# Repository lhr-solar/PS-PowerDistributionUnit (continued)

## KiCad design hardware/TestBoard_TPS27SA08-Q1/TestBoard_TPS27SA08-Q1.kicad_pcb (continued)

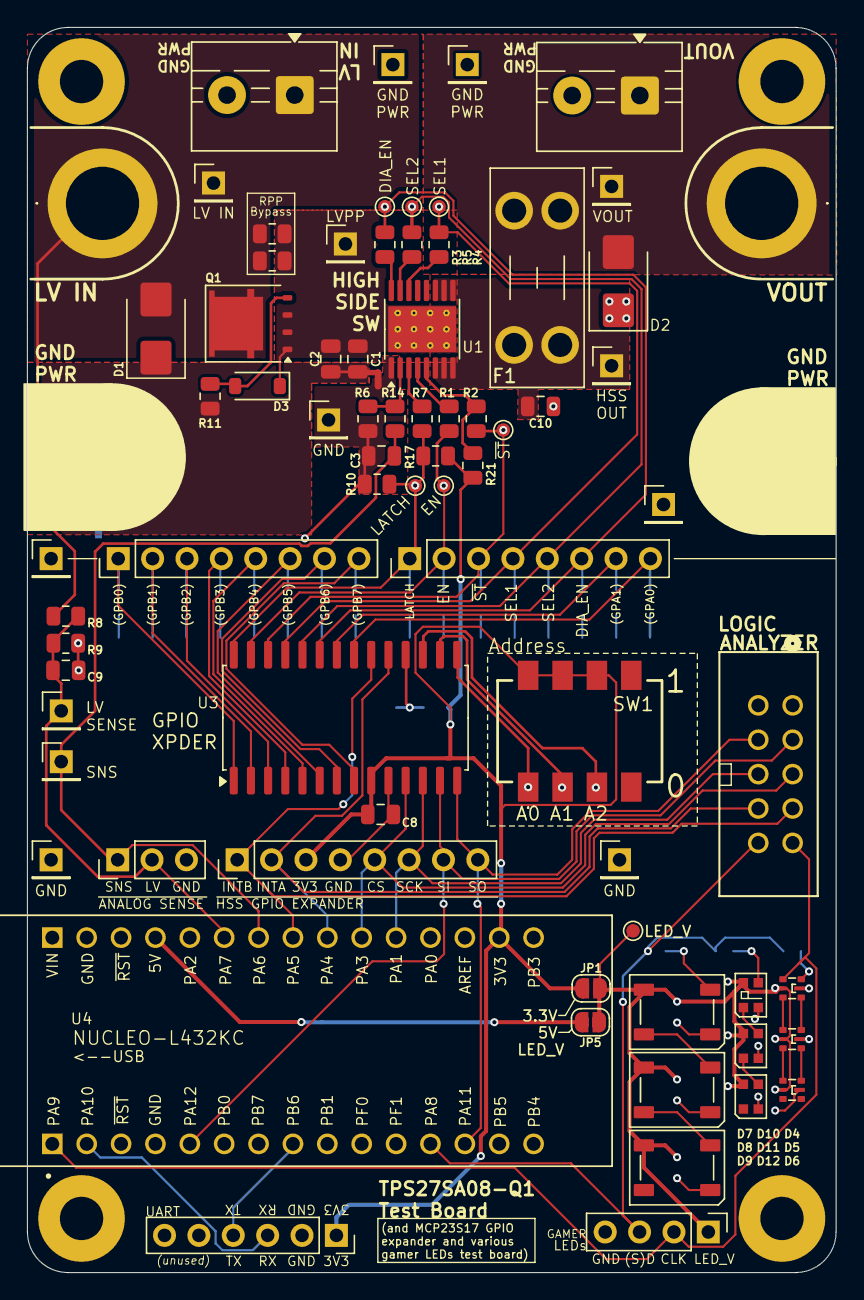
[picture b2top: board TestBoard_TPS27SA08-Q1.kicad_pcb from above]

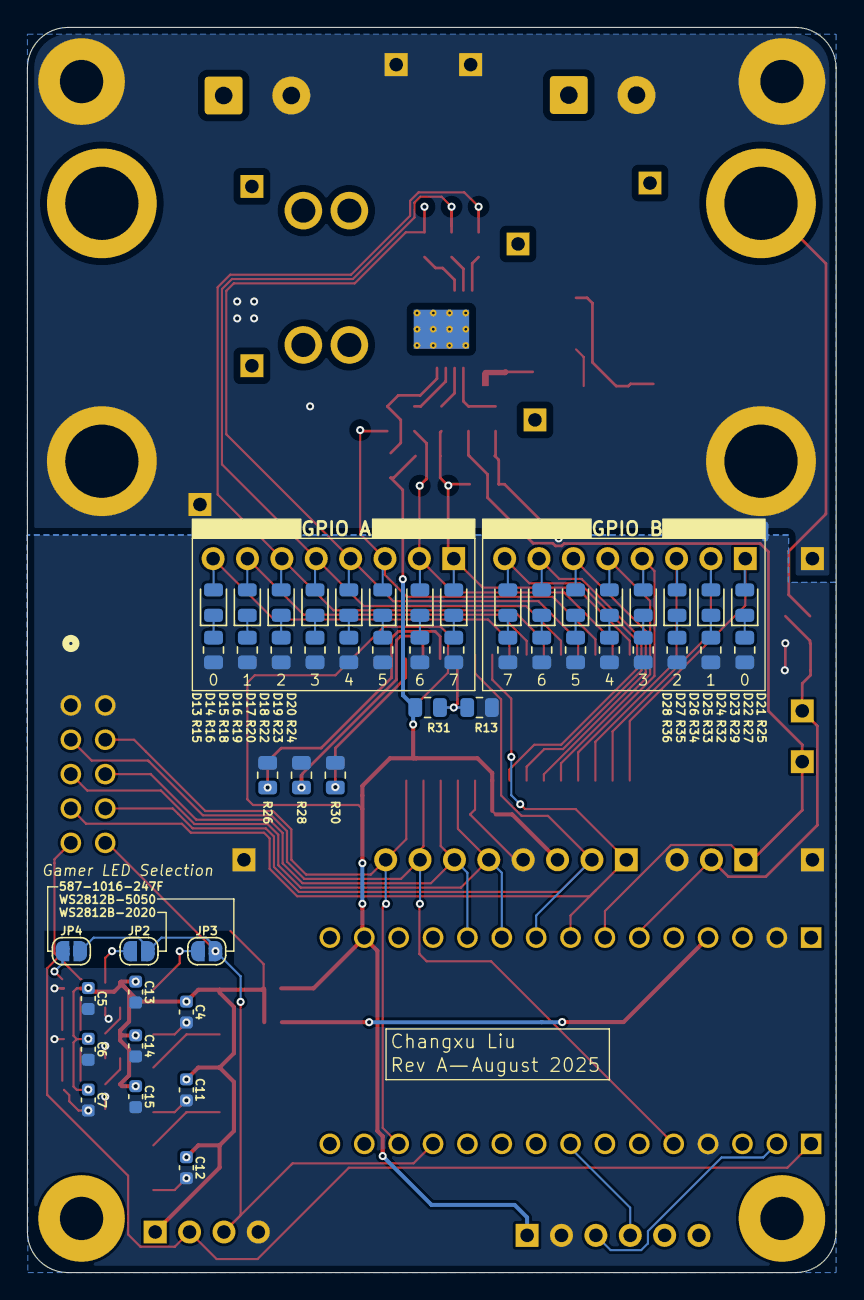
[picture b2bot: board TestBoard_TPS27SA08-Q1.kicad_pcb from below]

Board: 2 copper layers, 59.8 x 92.0 mm, 130 parts (50 on the bottom side), 76 nets.

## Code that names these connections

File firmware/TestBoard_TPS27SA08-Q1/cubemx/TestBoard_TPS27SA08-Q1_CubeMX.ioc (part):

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Mcu.Name=STM32L432K(B-C)Ux
Mcu.Package=UFQFPN32
Mcu.UserName=STM32L432KCUx
PA0.GPIOParameters=GPIO_Label
PA0.GPIO_Label=MCO [High speed clock in]
PA0.Mode=HSE-External-Clock-Source-for-LittleOrca
PA0.Signal=RCC_CK_IN
PA1.Mode=Full_Duplex_Master
PA1.Signal=SPI1_SCK
PA10.Mode=Asynchronous
PA10.Signal=USART1_RX
PA11.Mode=Full_Duplex_Master
PA11.Signal=SPI1_MISO
PA12.Mode=Full_Duplex_Master
PA12.Signal=SPI1_MOSI
PA13\ (JTMS-SWDIO).GPIOParameters=GPIO_Label
PA13\ (JTMS-SWDIO).GPIO_Label=SWDIO
PA13\ (JTMS-SWDIO).Mode=Serial_Wire
PA13\ (JTMS-SWDIO).Signal=SYS_JTMS-SWDIO
PA14\ (JTCK-SWCLK).GPIOParameters=GPIO_Label
PA14\ (JTCK-SWCLK).GPIO_Label=SWCLK
PA14\ (JTCK-SWCLK).Mode=Serial_Wire
PA14\ (JTCK-SWCLK).Signal=SYS_JTCK-SWCLK
PA15\ (JTDI).GPIOParameters=GPIO_Label
PA15\ (JTDI).GPIO_Label=VCP_RX
PA15\ (JTDI).Mode=Asynchronous
PA15\ (JTDI).Signal=USART2_RX
PA2.GPIOParameters=GPIO_Label
PA2.GPIO_Label=VCP_TX
PA2.Mode=Asynchronous
PA2.Signal=USART2_TX
PA3.Signal=GPIO_Output
PA4.Signal=GPIO_Output
PA5.Signal=GPIO_Output
PA6.Signal=ADCx_IN11
PA7.Signal=ADCx_IN12
PA8.Signal=S_TIM1_CH1
PA9.Signal=S_TIM1_CH2
PB3\ (JTDO-TRACESWO).GPIOParameters=GPIO_Label
PB3\ (JTDO-TRACESWO).GPIO_Label=LD3 [Green]
PB3\ (JTDO-TRACESWO).Signal=GPIO_Output
PB6.Mode=Asynchronous
PB6.Signal=USART1_TX
PC14-OSC32_IN\ (PC14).Mode=LSE-External-Oscillator
PC14-OSC32_IN\ (PC14).Signal=RCC_OSC32_IN
PC15-OSC32_OUT\ (PC15).Mode=LSE-External-Oscillator
PC15-OSC32_OUT\ (PC15).Signal=RCC_OSC32_OUT
RCC.HSE_VALUE=8000000
RCC.SYSCLKFreq_VALUE=32000000
RCC.SYSCLKSource=RCC_SYSCLKSOURCE_PLLCLK
board=NUCLEO-L432KC
boardIOC=true

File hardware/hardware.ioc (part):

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Mcu.Name=STM32G473C(B-C-E)Tx
Mcu.Package=LQFP48
Mcu.UserName=STM32G473CETx
PA0.Signal=GPIO_Output
PA15.Signal=GPIO_Output
PA3.Signal=GPIO_Output
PA4.Mode=NSS_Signal_Hard_Input
PA4.Signal=SPI1_NSS
PA5.Mode=Full_Duplex_Master
PA5.Signal=SPI1_SCK
PA6.Mode=Full_Duplex_Master
PA6.Signal=SPI1_MISO
PA7.Mode=Full_Duplex_Master
PA7.Signal=SPI1_MOSI
PA8.Signal=GPIO_Output
PA9.Signal=GPIO_Output
PB0.Signal=GPIO_Output
PB1.Signal=GPIO_Output
PB10.Signal=GPIO_Output
PB11.Signal=GPIO_Output
PB12.Mode=FDCAN_Activate
PB12.Signal=FDCAN2_RX
PB13.Mode=FDCAN_Activate
PB13.Signal=FDCAN2_TX
PB3.Signal=GPIO_Output
PB4.Signal=GPIO_Output
PB6.Signal=GPIO_Output
PB7.Signal=GPIO_Output
PC13.Signal=GPIO_Output
PC14-OSC32_IN.Signal=GPIO_Output
RCC.HSE_VALUE=8000000
RCC.SYSCLKFreq_VALUE=16000000
board=custom

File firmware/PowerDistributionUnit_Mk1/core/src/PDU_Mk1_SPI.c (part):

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
        __HAL_RCC_GPIOA_CLK_ENABLE();
        /**SPI1 GPIO Configuration
        PA5     ------> SPI1_SCK
        PA6     ------> SPI1_MISO
        PA7     ------> SPI1_MOSI
        */
        GPIO_InitStruct.Pin = GPIO_PIN_5|GPIO_PIN_6|GPIO_PIN_7;
        GPIO_InitStruct.Mode = GPIO_MODE_AF_PP;
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
        __HAL_RCC_GPIOB_CLK_ENABLE();
        /**SPI2 GPIO Configuration
        PB13     ------> SPI2_SCK
        PB14     ------> SPI2_MISO
        PB15     ------> SPI2_MOSI
        */
        GPIO_InitStruct.Pin = GPIO_PIN_13|GPIO_PIN_14|GPIO_PIN_15;
        GPIO_InitStruct.Mode = GPIO_MODE_AF_PP;
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
        __HAL_RCC_GPIOB_CLK_ENABLE();
        /**SPI3 GPIO Configuration
        PB3     ------> SPI3_SCK
        PB4     ------> SPI3_MISO
        PB5     ------> SPI3_MOSI
        */
        GPIO_InitStruct.Pin = GPIO_PIN_3|GPIO_PIN_4|GPIO_PIN_5;
        GPIO_InitStruct.Mode = GPIO_MODE_AF_PP;
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	__HAL_RCC_SPI1_CLK_DISABLE();

	/**SPI1 GPIO Configuration
	PA5     ------> SPI1_SCK
	PA6     ------> SPI1_MISO
	PA7     ------> SPI1_MOSI
	*/
	HAL_GPIO_DeInit(GPIOA, GPIO_PIN_5|GPIO_PIN_6|GPIO_PIN_7);
	}
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	__HAL_RCC_SPI2_CLK_DISABLE();

	/**SPI2 GPIO Configuration
	PB13     ------> SPI2_SCK
	PB14     ------> SPI2_MISO
	PB15     ------> SPI2_MOSI
	*/
	HAL_GPIO_DeInit(GPIOB, GPIO_PIN_13|GPIO_PIN_14|GPIO_PIN_15);
	}
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	__HAL_RCC_SPI3_CLK_DISABLE();

	/**SPI3 GPIO Configuration
	PB3     ------> SPI3_SCK
	PB4     ------> SPI3_MISO
	PB5     ------> SPI3_MOSI
	*/
	HAL_GPIO_DeInit(GPIOB, GPIO_PIN_3|GPIO_PIN_4|GPIO_PIN_5);
	}
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
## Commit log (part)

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2025-10-20 added external current sensor
2025-10-20 break tracks between HSSs and computery section to adjust spacing
2025-10-20 break bottom tracks between two sides of efuses
2025-10-20 break output tracks'
2025-10-20 shift sides of HSSs outwards
2025-10-20 one current sensor routing
2025-10-20 add local labels to HSS out sheet to help routing
2025-10-20 one quarter HSS routed
2025-10-20 one half HSS routed
2025-10-20 other side HSS add current sensor
2025-10-20 routing left side st and sns
2025-10-20 oops forgot sns5
2025-10-20 output traces
2025-10-21 st and adc traces on computery side, prep for pin/adc reassignment
2025-10-21 reassigned pins for connecting HSS to sensing
2025-10-21 routed sensing traces
2025-10-21 all connections routed
2025-10-21 reposition top side connectors (CAN, logic analyzer) and make board slightly taller
2025-10-23 adjust spacing on logic analyzer connectors
2025-10-23 readjust gnd plane to new size
2025-10-23 adjusted some traces
2025-10-25 status LEDs position adjustment, silkscreen, address DRC errors in that area
2025-10-25 rearrange 3.3V, 3.3VA, and GNDA test points, add labels for test points around LSOM, address DRC errors in area (and some LED ones that came back for some reason)
2025-10-25 cleaned up HSS config and regional area
2025-10-25 clean up and address DRC errors in input area
2025-10-25 adjust labels on input
2025-10-25 cleaning up things on/around LSOM
2025-10-25 top and bottom side silkscreen under LSOM
2025-10-25 add labels for some stuff
2025-10-25 make logic analyzer connector fancy
2025-10-25 gnd test points cleanup and labels, fix tiny logic analyzer connector issue
2025-10-25 address trace unconnected ends in DRC
2025-10-25 clear real clearance errors
2025-10-25 change input protection MOSFET
2025-10-25 clear drc warnings
2025-10-25 fix wonky traces
2025-10-25 excluded unnecessary clearance drc errors
2025-10-26 added HSS output labels
2025-10-26 add bypass to lv sense buffer
2025-10-26 change extra screw holes to standoffs
2025-10-26 add P/Ns to external current sensor symbol
2025-10-26 add labels for HSS pulls
2025-10-26 move gnd return connector upwards to free up more lv plane
2025-10-26 fill top layer under/around LSOM with GND
2025-10-26 add random stitching vias
2025-10-26 fillet corners in edge cuts
2025-10-26 add Darsh responsibility statement
2025-10-28 fix current sensor part number (used 5V version instead of 3.3V version)
2025-11-09 connect 3.3VA to ADC reference voltage
2025-11-09 export gerbers
2026-01-16 BBPDU Mk1 (#4)
    * add KiCad project
    * initial schematic
    * fix gamer LED footprint thing, thanks Gemini
    * change new symbol libraries to relative paths, thanks Gemini
    * schematic updates (found switch, LED resistor values, LV sense ADC pin filter, removed unnecessary parallel resistors, switched to new SR), addressed review comments (input fuse, 3.3V LED, SPI nami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
    * fix pages order, fix duplicate C25
2026-01-16 rename software folder to firmware
2026-01-31 fix makefile showing flash successful even when not (fix in Embedded-Sharepoint)
2026-01-31 MCP23S17 GPIO expander driver
2026-01-31 update makefile to give build failure message, remove madefile when running make clean
2026-01-31 add blank line to nix_thing.sh
2026-02-28 change ADC - reading voltage to resistor divider with option to reference to GND or 1.65V
2026-02-28 make input protection use b2b FETs
2026-02-28 change ADC AVDD and AGND connections to regular 3.3V and GND
2026-02-28 update KiCad-Sharepoint
2026-02-28 reroute LSOM SPI connections, repin logic analyzer connections
2026-02-28 change LSOM footprint to centered LSOM footprint, make centered LSOM footprint plated to address hidden pins on LSOM symbol
2026-02-28 update PCB from schematic
2026-02-28 layout/routing for input protection
2026-02-28 fix centered LSOM footprint 3D model, update footprint
2026-02-28 address DRC
2026-02-28 route a couple of missed connections (LV in connection to input prot IC, LV sense connection)
2026-02-28 change jumper to DNP resistor for ADC reference, routed
2026-02-28 reroute updated AVDD and AGND on ADCs
2026-02-28 add SRCLK_ENed connection to logic analyzer connector
2026-02-28 silkscreen fixes and stuff
2026-02-28 fix silkscreen labelling issues
2026-02-28 update schematic documentation, clean up, update titleblocks
2026-03-01 add LCSC P/N to libs
2026-03-01 update all symbols with LCSC P/N
2026-03-01 update PCB with LCSC P/Ns
2026-03-01 add center mounting hole
2026-03-01 correct fuse table
2026-03-02 change lv sense rdiv values to avoid extended components, update all pull-ups/-downs using 2.8k
2026-03-02 rotate nanofits for inwards clip
2026-03-02 NC the mounting holes (because Lakshay Gupta)
2026-03-02 fix shorted nets error from wrong size res symbol from resistor change
2026-03-02 assembly setup, change latch pull resistor DNP to latch off instead of auto retry by default
2026-03-02 change DNP for HSS diagnostics to default to current
2026-03-02 change DNP to disable HSS diagnostics by default (primarily use external current sensor)
2026-03-02 assembly setup stuff
2026-03-03 BBPDU Mk1 RevB (#6)
    * update adc reference to use internal reference (open) with jumper option
    * change ADC - reading voltage to resistor divider with option to reference to GND or 1.65V
    * change ADC AVDD and AGND connections to regular 3.3V and GND
    * make input protection use b2b FETs
    * update KiCad-Sharepoint
    * update LeaderSOM symbol and SPI pinout (bottom) - need to swap SPI2 and SPI3 names, remove local library copy of LeaderSOM symbol
2026-03-03 add new PDTestBreakout project
2026-03-06 fix TEST capitalization in makefile, change formatting
2026-03-06 add MCP23S17 datasheet
2026-03-06 change pin type to uint16_t because HAL convention
2026-03-07 add register descriptions
2026-03-07 add enum comments
2026-03-07 move defines out of c file to header file
2026-03-07 update function documentation comments, add comments for static functions in c file
2026-03-07 remove unnecessary comment
2026-03-07 function comment update
2026-03-07 change functions to return status
2026-03-08 update documentation returning status, other things
2026-03-08 improve addressing comment
2026-03-08 move uint8_to_binary_str to utilities file
2026-03-08 add pin defines to file
2026-03-13 add descriptions to tests
2026-03-31 add todo
2026-03-31 in progress ADC driver
2026-04-02 add basic RTOS support, update a few tests alongside
2026-04-02 fix hard coded fsr value
2026-04-02 fix reading zero registers in Init function (still in progress)
2026-04-04 RTOSify MCP23S17 driver
2026-04-04 update constant names, update comments, clean up
2026-04-04 update MCP23S17 init function for less arguments, change configuration to use lshift, comments and stuff, cleanup
2026-04-05 updated MCP23S17 test for RTOS - untested as don't have TestBoard_TPS27SA08-Q1 with me, just getting to compiling to test build action
2026-04-05 add github build action
2026-04-05 add github build action (attempt 3)
2026-04-05 add github build action (attempt 4)
2026-04-05 add github build action (attempt 5)
2026-04-05 add github build action (attempt 6)
2026-04-05 remove commies.c
2026-04-05 add units for SPI delays
2026-04-05 add units to SPI delay names
2026-04-05 fix tests
2026-04-05 change Pins, SPI, and UART files structure
2026-04-06 add device and data null check
2026-04-06 move encoding of data before taking SPI mutex
2026-04-06 lakshay being picky picky picky
2026-04-06 fix spi cs and mutex not returning to original state if spi transmission semaphore times out
2026-04-06 fix discarding status return if not 🙂 (as now there's more statuses)
2026-04-06 fix spi cs and mutex not returning to original state if HAL spi function isn't happy
2026-04-06 lakshay lies
2026-04-06 add checks for spi mutex and sempahore null
2026-04-06 move SPI interrupt functions ot SPI file
2026-04-06 move SPI mutex and done semaphore setup to function in SPI file
2026-04-06 make SPI interrupt priority a define
2026-04-07 add flash-uart to makefile
2026-04-11 must've forgotten to include this in update to define name from before
2026-04-12 ADC driver init function, calibration register functions
2026-04-12 move private functions to c file
2026-04-12 fix dummy send failures potential to lock up SPI mutex
2026-04-12 Add embedded sharepoint, MCP23S17 driver and basic tests (#5)
    * rename software folder to firmware
    * set up embedded sharepoint
    * fix makefile showing flash successful even when not (fix in Embedded-Sharepoint)
    * MCP23S17 GPIO expander driver
    * update makefile to give build failure message, remove madefile when running make clean
    * add blank line to nix_thing.sh
2026-04-25 fix reset command delay in wrong spot
2026-04-25 add other enums for SPI mutex/semaphore timeouts
2026-04-25 move PDU_Mk1_Clock.h to core folder
2026-04-25 change numbers in one test to be defines, make reference voltage value a define, remove debug return in init that resulted in no configuration written
2026-04-25 update adc init function to update all channels, address task stack overflow issues in test
2026-04-25 oops didn't actually incrase stack size before
2026-04-25 update ADS131M08Q1 tests (and LSOM blinky printy)
2026-04-25 reorder function definitions in c file to match header
2026-04-25 add documentation comments, fix declaration name of a transmit function
2026-04-26 fix SPI potentially being trapped if CS or mutex not released in case of failure
2026-04-26 remove magic number
2026-05-08 add current sensing with ADC initialization moved to
2026-05-08 clean up
2026-05-10 update Convert test and initialization for both ADCs on BBPDU
2026-05-10 add check for SPI and SPI RTOS stuff set up properly before attempting talking with ADC
2026-05-10 update embedded sharepoint
2026-05-10 ADS131M08-Q1 driver (#7)
    * in progress ADC driver
    * add basic RTOS support, update a few tests alongside
    * fix hard coded fsr value
    * fix reading zero registers in Init function (still in progress)
    * remove commies.c
    * add _t to enum and struct type names
2026-05-10 add all the ADS131M08-Q1 driver stuff from before...
2026-05-10 attempt add github action
2026-05-10 try github action again
2026-05-10 fix copy paste errors in SPI
2026-05-10 remove erroneous comment in GPIO
2026-05-10 fix convoluted conversion code
2026-05-10 ADS131M08-Q1 driver (#10)
    (see PR #7)
    * add all the ADS131M08-Q1 driver stuff from before...
    * attempt add github action
    * try github action again
    * attempt github action again
    * fix copy paste errors in SPI
2026-05-10 current sensing code
2026-05-10 fix copy paste errors in current sensing header
2026-05-11 remove underscore between current sensing
2026-05-11 HSS control
2026-05-17 add fs
2026-05-17 remove disable interrupts from test error handler
2026-05-17 add description and example part number, add datasheet
2026-05-17 add function descriptions, fix typo in driver description
2026-05-17 remove debug printf statements
2026-05-17 add warning on keeping everything within one task for HSSControl to description
2026-05-20 remove filtering faulted channels from output en
2026-05-20 add status enum instead of true false for returns
2026-06-22 add SPI reconfiguration function before communicating with ADC
2026-06-22 add SPI reconfiguration function before communicating with SR
2026-06-22 add functions for getting EN and fault state of a channel (for CAN stuff)
2026-06-22 update indentation
2026-06-23 corrected LSOM pins
2026-06-24 HSS control (#12)
    * HSS control
    * remove disable interrupts from test error handler
    * add description and example part number, add datasheet
    * update delay
    * add function descriptions, fix typo in driver description
    * remove debug printf statements
2026-06-25 Current sensing (#11)
    * current sensing code
    * fix copy paste errors in current sensing header
    * make initial offset calculation average of multiple samples
    * remove underscore between current sensing
    * add fs
    * add conditional to avoid trying to use inaccessible ADC on rev A (pinout issue)
2026-06-25 CAN and tasks stuff
2026-06-25 remove old tests because causing Github check to fail
2026-06-25 fix MakeAllTests github check
2026-06-26 remove redundant while(1)
2026-06-26 fix HSS Control task description
2026-06-26 remove unused print status task for now
2026-06-26 blank lines
